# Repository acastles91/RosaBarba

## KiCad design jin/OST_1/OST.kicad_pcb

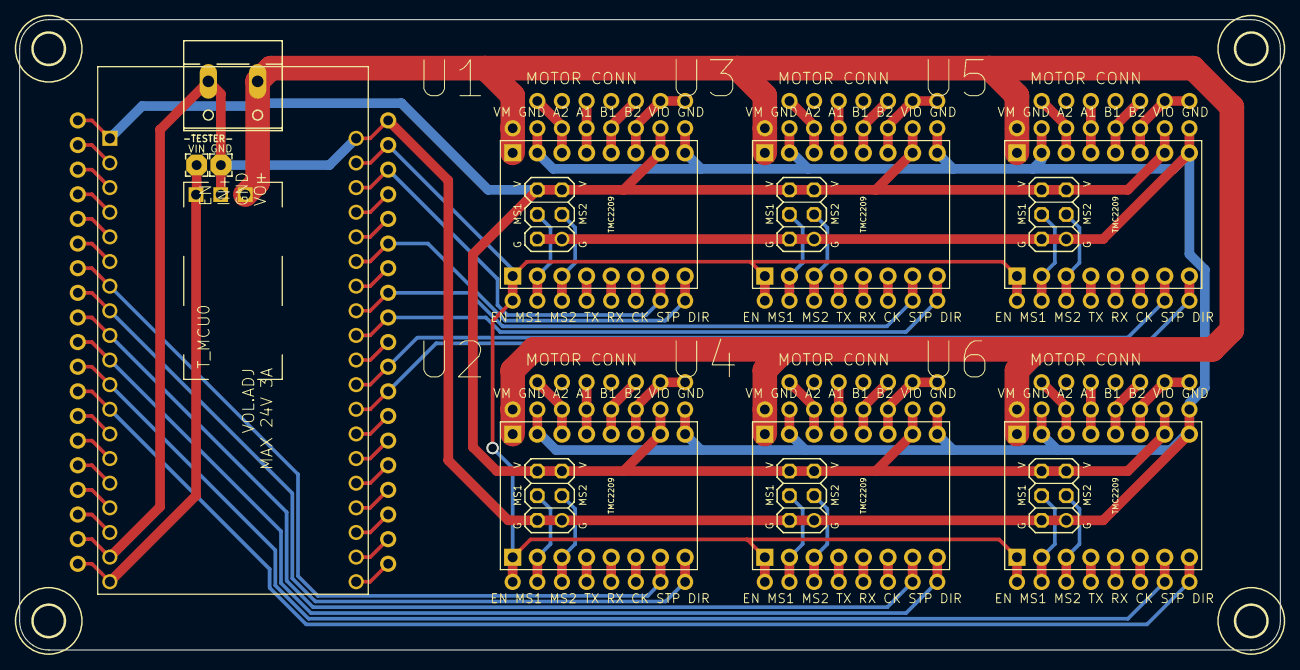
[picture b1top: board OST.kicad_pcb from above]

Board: 2 copper layers, 130.0 x 65.0 mm, 41 parts (0 on the bottom side), 92 nets.

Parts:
H1, H2, H3, H4: MOUNT-HOLE3.2; 3,2
MCU0: ESP32-DEVKITC-32D; MODULE_ESP32-DEVKITC-32D
PAD16, PAD17: 2,15_1,0
T_MCU0: VOL_ADJ; FREEVOL
U1, U2, U3, U4, U5, U6: TMC2209_V3.1; TMC2209
U$1, U$2: PINHD_1X19; 19
U$3, U$4, U$11, U$12, U$15, U$16, U$23, U$24, U$31, U$32, U$39, U$40: PINHD_1X8; 8
U$5, U$13, U$17, U$25, U$33, U$41: PINHD_3X2; MA03-2
U$6, U$14, U$18, U$26, U$34, U$42: PINHD_1X7; 7
X1: W237-132

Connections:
3V3: MCU0.1, U1.P$VIO, U2.P$VIO, U3.P$VIO, U4.P$VIO, U5.P$VIO, U6.P$VIO, U$2.P$19, U$3.P$7, U$5.5, U$5.6, U$11.P$7, U$13.5, U$13.6, U$15.P$7, U$17.5, U$17.6, U$23.P$7, U$25.5, U$25.6, U$31.P$7, U$33.5, U$33.6, U$39.P$7, U$41.5, U$41.6
5V: MCU0.19, PAD17.1, T_MCU0.P3, U$2.P$1
A1: U1.P$A1, U$3.P$4, U$6.P$3
A2: U1.P$A2, U$3.P$3, U$6.P$1
A5: U2.P$A2, U$11.P$3, U$14.P$1
A6: U2.P$A1, U$11.P$4, U$14.P$3
A7: U3.P$A2, U$15.P$3, U$18.P$1
A8: U3.P$A1, U$15.P$4, U$18.P$3
A11: U5.P$A2, U$23.P$3, U$26.P$1
A12: U5.P$A1, U$23.P$4, U$26.P$3
A15: U4.P$A2, U$31.P$3, U$34.P$1
A16: U4.P$A1, U$31.P$4, U$34.P$3
A19: U6.P$A2, U$39.P$3, U$42.P$1
A20: U6.P$A1, U$39.P$4, U$42.P$3
A_DIR: MCU0.25, U1.P$DIR, U$1.P$6, U$4.P$1
A_MS1: U1.P$MS1, U$4.P$7, U$5.4
A_MS2: U1.P$MS2, U$4.P$6, U$5.3
A_STEP: MCU0.22, U1.P$STEP, U$1.P$3, U$4.P$2
B1: U1.P$B1, U$3.P$5, U$6.P$5
B2: U1.P$B2, U$3.P$6, U$6.P$6, U$6.P$7
B5: U2.P$B1, U$11.P$5, U$14.P$5
B6: U2.P$B2, U$11.P$6, U$14.P$6, U$14.P$7
B7: U3.P$B1, U$15.P$5, U$18.P$5
B8: U3.P$B2, U$15.P$6, U$18.P$6, U$18.P$7
B11: U5.P$B1, U$23.P$5, U$26.P$5
B12: U5.P$B2, U$23.P$6, U$26.P$6, U$26.P$7
B15: U4.P$B1, U$31.P$5, U$34.P$5
B16: U4.P$B2, U$31.P$6, U$34.P$6, U$34.P$7
B19: U6.P$B1, U$39.P$5, U$42.P$5
B20: U6.P$B2, U$39.P$6, U$42.P$6, U$42.P$7
B_DIR: MCU0.8, U2.P$DIR, U$2.P$12, U$12.P$1
B_MS1: U2.P$MS1, U$12.P$7, U$13.4
B_MS2: U2.P$MS2, U$12.P$6, U$13.3
B_STEP: MCU0.7, U2.P$STEP, U$2.P$13, U$12.P$2
C_DIR: MCU0.28, U3.P$DIR, U$1.P$9, U$16.P$1
C_MS1: U3.P$MS1, U$16.P$7, U$17.4
C_MS2: U3.P$MS2, U$16.P$6, U$17.3
C_STEP: MCU0.27, U3.P$STEP, U$1.P$8, U$16.P$2
D_DIR: MCU0.10, U4.P$DIR, U$2.P$10, U$32.P$1
D_MS1: U4.P$MS1, U$32.P$7, U$33.4
D_MS2: U4.P$MS2, U$32.P$6, U$33.3
D_STEP: MCU0.9, U4.P$STEP, U$2.P$11, U$32.P$2
EN: MCU0.21, U1.P$EN, U2.P$EN, U3.P$EN, U4.P$EN, U5.P$EN, U6.P$EN, U$1.P$2, U$4.P$8, U$12.P$8, U$16.P$8, U$24.P$8, U$32.P$8, U$40.P$8
E_DIR: MCU0.31, U5.P$DIR, U$1.P$12, U$24.P$1
E_MS1: U5.P$MS1, U$24.P$7, U$25.4
E_MS2: U5.P$MS2, U$24.P$6, U$25.3
E_STEP: MCU0.30, U5.P$STEP, U$1.P$11, U$24.P$2
F_DIR: MCU0.12, U6.P$DIR, U$2.P$8, U$40.P$1
F_MS1: U6.P$MS1, U$40.P$7, U$41.4
F_MS2: U6.P$MS2, U$40.P$6, U$41.3
F_STEP: MCU0.11, U6.P$STEP, U$2.P$9, U$40.P$2
GND: MCU0.18, MCU0.20, PAD16.1, T_MCU0.P2, U1.P$GND@IO, U1.P$GND@M, U2.P$GND@IO, U2.P$GND@M, U3.P$GND@IO, U3.P$GND@M, U4.P$GND@IO, U4.P$GND@M, U5.P$GND@IO, U5.P$GND@M, U6.P$GND@IO, U6.P$GND@M, U$1.P$1, U$2.P$2, U$3.P$2, U$3.P$8, U$5.1, U$5.2, U$11.P$2, U$11.P$8, U$13.1, U$13.2, U$15.P$2, U$15.P$8, U$17.1, U$17.2, U$23.P$2, U$23.P$8, U$25.1, U$25.2, U$31.P$2, U$31.P$8, U$33.1, U$33.2, U$39.P$2, U$39.P$8, U$41.1, U$41.2, X1.2
unnamed: U1.P$CLK, U$4.P$3
unnamed: MCU0.38, U$1.P$19
unnamed: U2.P$CLK, U$12.P$3
unnamed: MCU0.2, U$2.P$18
unnamed: MCU0.3, U$2.P$17
unnamed: MCU0.4, U$2.P$16
unnamed: MCU0.5, U$2.P$15
unnamed: MCU0.6, U$2.P$14
unnamed: MCU0.13, U$2.P$7
unnamed: MCU0.14, U$2.P$6
unnamed: MCU0.15, U$2.P$5
unnamed: MCU0.16, U$2.P$4
unnamed: MCU0.17, U$2.P$3
unnamed: U3.P$CLK, U$16.P$3
unnamed: MCU0.37, U$1.P$18
unnamed: MCU0.36, U$1.P$17
unnamed: MCU0.35, U$1.P$16
unnamed: MCU0.34, U$1.P$15
unnamed: MCU0.33, U$1.P$14
unnamed: MCU0.32, U$1.P$13
unnamed: MCU0.29, U$1.P$10
unnamed: MCU0.26, U$1.P$7
unnamed: MCU0.24, U$1.P$5
unnamed: U5.P$CLK, U$24.P$3
unnamed: U4.P$CLK, U$32.P$3
unnamed: U6.P$CLK, U$40.P$3
P$444: MCU0.23, U$1.P$4
RX: U1.P$RX, U$4.P$4
RX2: U2.P$RX, U$12.P$4
RX3: U3.P$RX, U$16.P$4
RX5: U5.P$RX, U$24.P$4
RX7: U4.P$RX, U$32.P$4
RX9: U6.P$RX, U$40.P$4
TX: U1.P$TX, U$4.P$5
TX2: U2.P$TX, U$12.P$5
TX3: U3.P$TX, U$16.P$5
TX5: U5.P$TX, U$24.P$5
TX7: U4.P$TX, U$32.P$5
TX9: U6.P$TX, U$40.P$5
VIN: T_MCU0.P1, U1.P$VM, U2.P$VM, U3.P$VM, U4.P$VM, U5.P$VM, U6.P$VM, U$3.P$1, U$11.P$1, U$15.P$1, U$23.P$1, U$31.P$1, U$39.P$1, X1.1

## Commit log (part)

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2022-07-28 Working with duration
2022-12-15 last working
2022-12-15 Second frame, speeds and direction approved by Nils
2023-04-28 Only one motor, not using AccelStepper, much cleaner step wave
2023-06-15 Agnieska Polska before moving back to Rosa
2023-06-15 modified, added second motor
2023-07-12 Two motors, no libraries, for Rosa Barba
2023-07-12 Speeds approved by Nils
2026-06-18 fixed startup
2026-06-18 added phonetic-script
2026-06-18 added Spiral
2026-06-18 added Spiral 2
2026-06-18 fixed normal install script
